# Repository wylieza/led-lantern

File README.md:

# led-lantern
Loadshedding Light Project

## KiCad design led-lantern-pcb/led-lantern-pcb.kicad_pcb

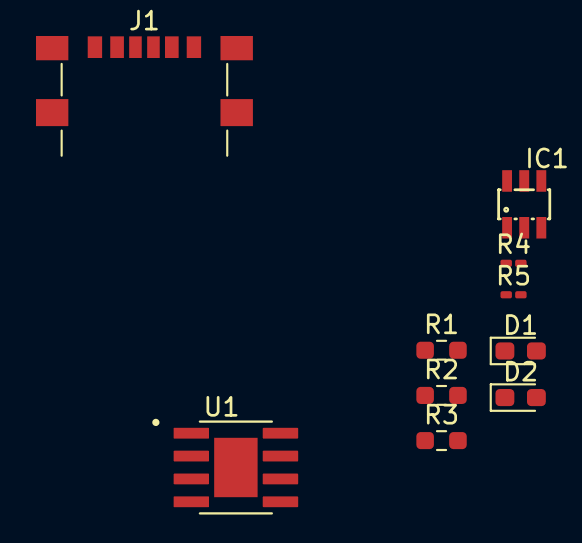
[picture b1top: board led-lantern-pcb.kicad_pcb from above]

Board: 2 copper layers, 10 parts (0 on the bottom side), 9 nets, no tracks yet.

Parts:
D1, D2: LED; LED_0603_1608Metric_Pad1.05x0.95mm_HandSolder
IC1: DW01A; SOT23-6
J1: USB_C_Receptacle_PowerOnly_6P; USB_C_Receptacle_GCT_USB4135-GF-A_6P_TopMnt_Horizontal
R1: 1R2; R_0603_1608Metric_Pad0.98x0.95mm_HandSolder
R2, R3: 1k; R_0603_1608Metric_Pad0.98x0.95mm_HandSolder
R4, R5: 5k1; R_0201_0603Metric_Pad0.64x0.40mm_HandSolder
U1: TP4056; SOP127P600X175-9N

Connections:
+5V: D1.2 (A), D2.2 (A), J1.A9 (VBUS), J1.B9 (VBUS), U1.4 (VCC), U1.8 (CE)
GND: J1.A12 (GND), J1.B12 (GND), R1.2, R4.2, R5.2, U1.1 (TEMP), U1.3 (GND)
unnamed: D1.1 (K), R2.1
unnamed: D2.1 (K), R3.1
unnamed: J1.A5 (CC1), R5.1
unnamed: J1.B5 (CC2), R4.1
unnamed: R1.1, U1.2 (PROG)
unnamed: R2.2, U1.7 (~CHRG)
unnamed: R3.2, U1.6 (~STDBY)

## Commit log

2023-02-21 initial commit - getting project started
2023-02-27 TP4056 and USB C (power only). Started on the DW01A circuit
2023-04-27 schematic into blocks and added auto power path control to schematic
